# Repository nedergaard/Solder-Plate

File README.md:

🚀 This is a fork of [arwidcool/Solder-Plate](https://github.com/arwidcool/Solder-Plate). Please contribute to the original repository instead of this one.

---

# Solder Plate Controller with Detachable Hotplate

This repository contains the source code and design files for a Solder Plate Controller and detachable hotplate. The processor used is the ATmega4809 and is based on the work of DerSpatz. https://github.com/DerSpatz/PCB-reflow-solder-heat-plate

## Features
- Precise temperature control for soldering SMD components. with support of **up to 6 thermistors**.
- Cheap and widely available MCU- Atmega4809 and low BOM cost
- Custom PCB design with 2 versions: single area control (Completed) and 4 independent heating zones control(In works)
- Detacabale hotplate allows for use of new heatplate designs including larger ones
- Programming via USB
- PlatformIO integration for streamlined development.
- wifi via esp8266-12f module (with wifi version - In Development).
- Based on Reflow Hotplate by DerSpatz with some improvements
- Oled for menu navigation, debugging, and thermistor info
- TFT for reflow profile target and actual temp
- 4 buttons for menu navigation
- Current sense IC for current monitoring
- 3 indicator LED's. They work for both menu and REFLOW profiles (blinking while on the current stage and solid once the profile stage is complete).
- Buzzer for complete notification
- Buck- Converter for input voltage, allowing up to 24V in
- 24V+ rated input voltage stage components allowing  up to 24V to be used (Depending on powersupply trip option the "max" pwm needs to be lowered to not trip power suppply safety)
- Optional fan for cooling stage (not yet installed)
= Included are files for a case and a guard for the detachable plate terminal guard.

## Getting Started

### Prerequisites

- PlatformIO Core or PlatformIO IDE.
- ATmega4809 microcontroller and all the BOM components
- Basic soldering tools and electronic assembly skills.
- Access to a PCB manufacturing service or soldering equipment (solder paste, hot air gun, tweezers)
- Some basic technical skills

### Hardware Setup

*** MAKE SURE YOU ORDER THE HOTPLATE IN BLACK. IT WILL NOT DISCOLOR AND HOLDS UP A LOT BETTER TO HEAT CYCLES ***

1. **PCB Fabrication:** Fabricate the PCB using the provided gerber files. You can use these to order the naked PCB from services like JLCPCB. 
2. **Component Assembly:** Solder the components onto the PCB as per the schematic or choose a SMT assembly service like the ones from JLCPCB
3. **Power Supply Connection:** Choose a suitable power supply. 12V 5A tested, 24v 5A compatible. Use of more then 5A requires a appropriate FUSE to be chosen and solder on place of F1

### Preparing the ATmega4809

Before programming the ATmega4809, it needs to be flashed with a default bootloader.

1. **Bootloader Flashing:**

Same process as DerSpatz Solder plate with some changes to the bootloader settingffs:

The MCU can be programmed with JTAG2UPDI (https://github.com/ElTangas/jtag2updi). For programming, you need an Arduino with ATMEGA328p (Uno or Nano), some wires, a 4.7k resistor and a 10µF capacitor or 120 Ohm resistor to disable the auto-reset.

JCM from the Discord explained the process pretty good:

- Download/Clone this project: https://github.com/ElTangas/jtag2updi and rename the folder "source" to "jtag2updi" (otherwise the Arduino IDE won't like it)
- Open jtag2updi/jtag2updi.ino in your Arduino IDE
- Configure the flasher options for your Arduino Nano and flash it
- Connect D6 of your Arduino Nano over the 4.7kOhm resistor to the UPDI pin of the board and 5V to 5V and GND to 0V
- Add the MegaCoreX hardware package to the Ardunio IDE (see https://github.com/MCUdude/MegaCoreX#how-to-install)
- Select the options for the programmer **(Board: ATmega4809, Clock: Internal 16 MHz, BOD: 2.6V or 2.7V, EEPROM: retained, Pinout: 48 pin standard, Reset pin: Reset, Bootloader:Optiboot:Uart0(Defualt pins))** and select the port of your Ardunio Nano as Port
- Make sure the programmer selected is SerialUPDI or JTAG2UPDI
- Select Burn Bootloader and see if it runs through

2. **MicroUSB Programming And Firmware Upload:**

   - **Using Platformio:**
   1. After flashing the bootloader, the ATmega4809 can be programmed via the microUSB connection using PlatformIO by building the project and upload
  
   - **Using AVRDude:**
   1. Folow instructions on : https://github.com/ElTangas/jtag2updi?tab=readme-ov-file#using-with-avrdude
   2. Example : avrdude -c jtag2updi -P com7 -p t1614
  
   - **Using AVRDUDESS (AVRDUDE with GUI interface) -- This section many not be completley finished:**
   1. Download and install AVRDUDE https://download-mirror.savannah.gnu.org/releases/avrdude/
   2. Download AVRDUDESS : https://github.com/ZakKemble/AVRDUDESS
   3. Choose the programmer as arduino
   4. Choose the MCU as ATmega4809
   5. Choose the COMPORT where the Solder Plate Controller is connected to
   6. Choose the Flash binary in the programming directory -> set to Write
   7. Choose "Write" on the Flash option and press "Go"

3. **Setting up the controller**
   1. Order 100K NTC Glass thermistors  Use for dev was : 100K Ohm Resistor NTC 3950->  https://www.aliexpress.com/item/32862228715.html?spm=a2g0o.order_list.order_list_main.11.1f0a1802Lw8YGL
   2. Using either the potentiometer or soldering the resistor beside it choose the resistor reference value (2.5Kohm is standard)
   3. You can modify the thermistor settings in Global.ccp file, it is all explained in there
   4. Attach the sensors to the hotplate using High temp Kapton Tape
   5. Reccomended is 3 sensors on the bottom middle of plate all with 3 different refernece resistor values for accuracy across all temperature ranges and 1 thermistor held by a pair of helping hangs placed so the head touches somewhere on the PCB to be refllowed
   By default this is set as thermistor 1:
   6. Link to 2.0 inch TFT -> https://www.aliexpress.com/item/1005002363748586.html?spm=a2g0o.order_list.order_list_main.5.165d1802Amz1I7  (8 pin version) -> 7 Pin version can also be used 
   7. Link to 0.96 OLED -> https://www.aliexpress.com/item/32957309383.html?spm=a2g0o.order_list.order_list_main.17.662c1802iqqiSE  (Choose OLD design SSD1306)

   *** IMPORTANT: Thermistors 1 is ONLY available on the hotplate. Thermistor 6 is only available on the controller via connector 5**

   You can solder the thermistors directly on the hotplatte or use them with the connector. Please update the thermistor settings to the way you have them set-up.

   Here are the defualt thermistor settings, The assume that the thermistors are soldered on the plate for 1,2,3: 
   Thermistors 6 on the connector number 5, touching the PCB to be soldered.

   Thermistor thermistor1(THERMISTOR1_PIN, 2545, ThermistorZ_Placement::ON_PCB, ThermistorXY_Placement::MIDDLE);          // -> 2545ohm set refrence -> This thermistor is set directly touching the PCB to be soldered
   Thermistor thermistor2(THERMISTOR2_PIN, 9100, ThermistorZ_Placement::BOTTOM, ThermistorXY_Placement::MIDDLE_LOW_TEMP);          //- > 9100 ohm set refrence Best accuracy around 90C -> This thermistor is used for the lower end of the temp scale  
   Thermistor thermistor3(THERMISTOR3_PIN, 2040, ThermistorZ_Placement::BOTTOM, ThermistorXY_Placement::MIDDLE); // -> 2.5Kohm best middleground
   Thermistor thermistor4(THERMISTOR4_PIN, 564, ThermistorZ_Placement::BOTTOM, ThermistorXY_Placement::MIDDLE_HIGH_TEMP); //-> 564Kohm set refrence // 564R reference = Best accuracy around 210C

   If you wish to only use the connectors use 2,3,4 and update the Globals .cpp to match your settings
      
   The set resistence is measured between a GND point anywhere on the board and the LEFT pin of the connector with the thermistor UNPLUGGED and the MODULE POWERED OFF!!!!

   you can measure and set those to the preset values or modify the values in globals.ccp to match your thermistors.

   If a thermistor is set to bottom a automatic scaling factor for the difference difference in plate temp is set that was aquired through lots of datalogging and computations

   If a thermistor is set to SIDE there is no scaling factor and will throw off the reading acorss the center of the plate (overall will be lower)

   When using the Thermistor with placement "ON_PCB" That thermistor has a weighting factor of 10 and has the biggest effect on the read temperature.

   The normal weighting factor is between 0.1 and 1.5 for the others.

### Software Installation

1. **Clone the Repository:**
   ```bash
   git clone https://github.com/arwidcool/Solder-Plate
   cd Solder-Plate
2. **Import in vscode**
To open a PlatformIO project in VSCode with the PlatformIO extension, follow these steps:

1. Launch VSCode and ensure that you have the PlatformIO extension installed. If not, you can install it from the VSCode marketplace.
2. Open the VSCode command palette by pressing Ctrl+Shift+P (Windows/Linux) or Cmd+Shift+P (Mac).
3. In the command palette, type "PlatformIO: Open" and select the "PlatformIO: Open" command from the list.
4. Navigate to the root folder of your PlatformIO project using the file explorer that appears.
5. Select the folder and click "Open" to open the PlatformIO project in VSCode.

### Usage

Power On: Connect the controller with a 12V 5A(Tested working) or 24V 5A PSU (Untested)
Set Profile: Navigate the menu and choose the desired reflow profile
Start Soldering: Place your PCB and components on the hotplate and start the profile

### Customization

Feel free to modify the firmware and PCB design to suit your specific needs.

### Contributing
Contributions are welcome. Please follow standard procedures for contributing to open-source projects.

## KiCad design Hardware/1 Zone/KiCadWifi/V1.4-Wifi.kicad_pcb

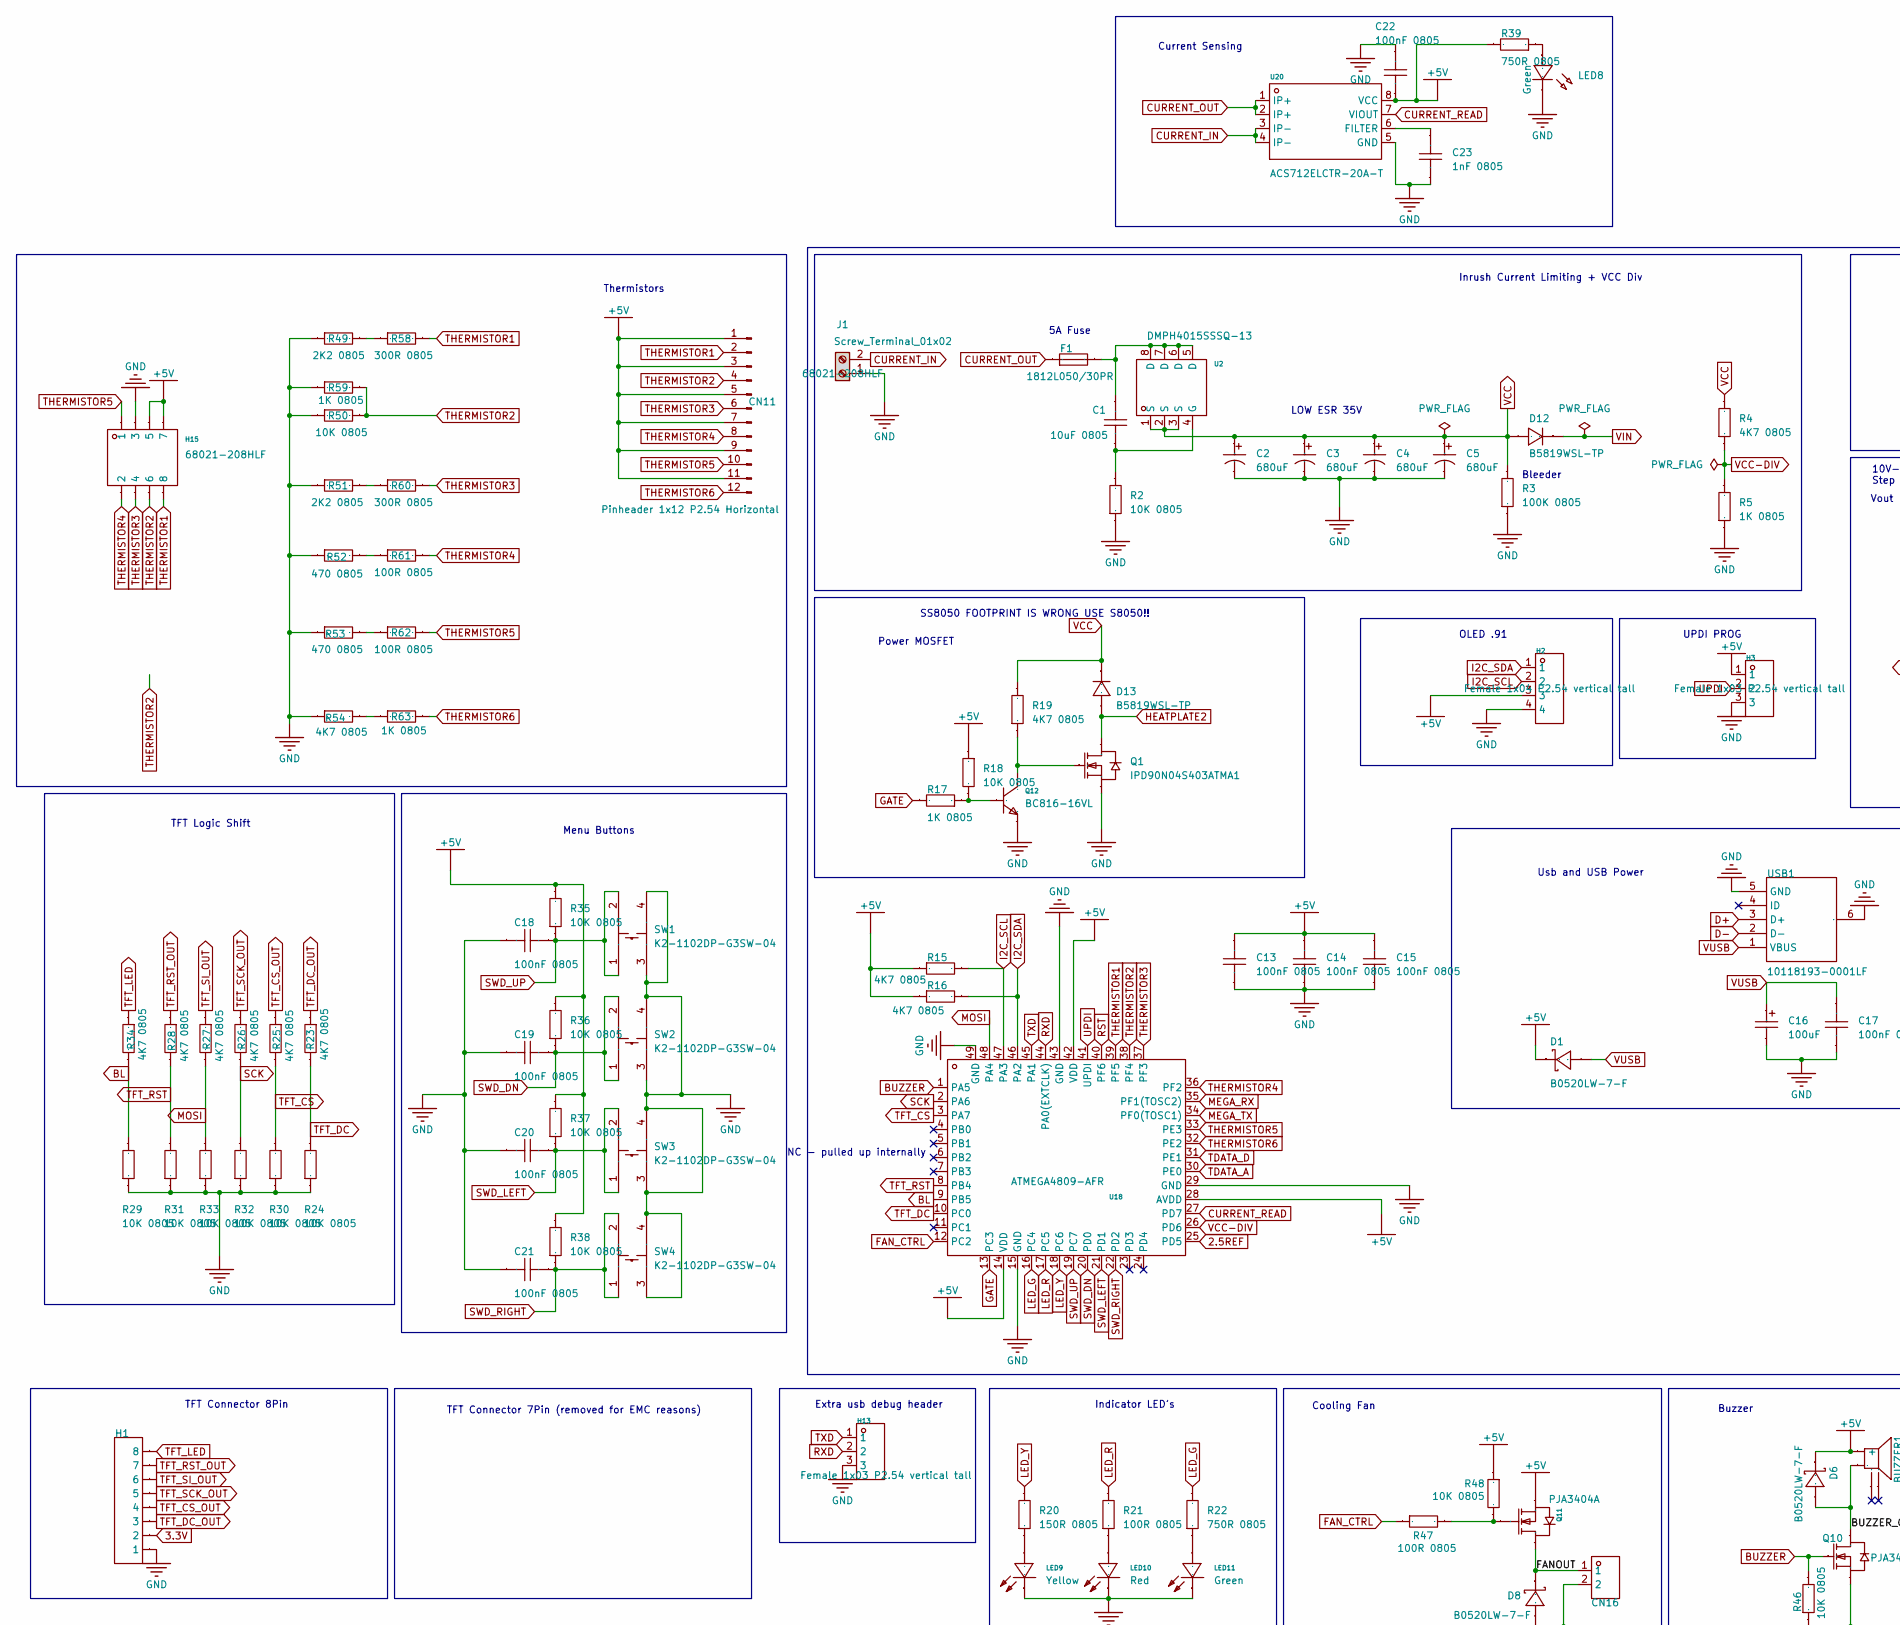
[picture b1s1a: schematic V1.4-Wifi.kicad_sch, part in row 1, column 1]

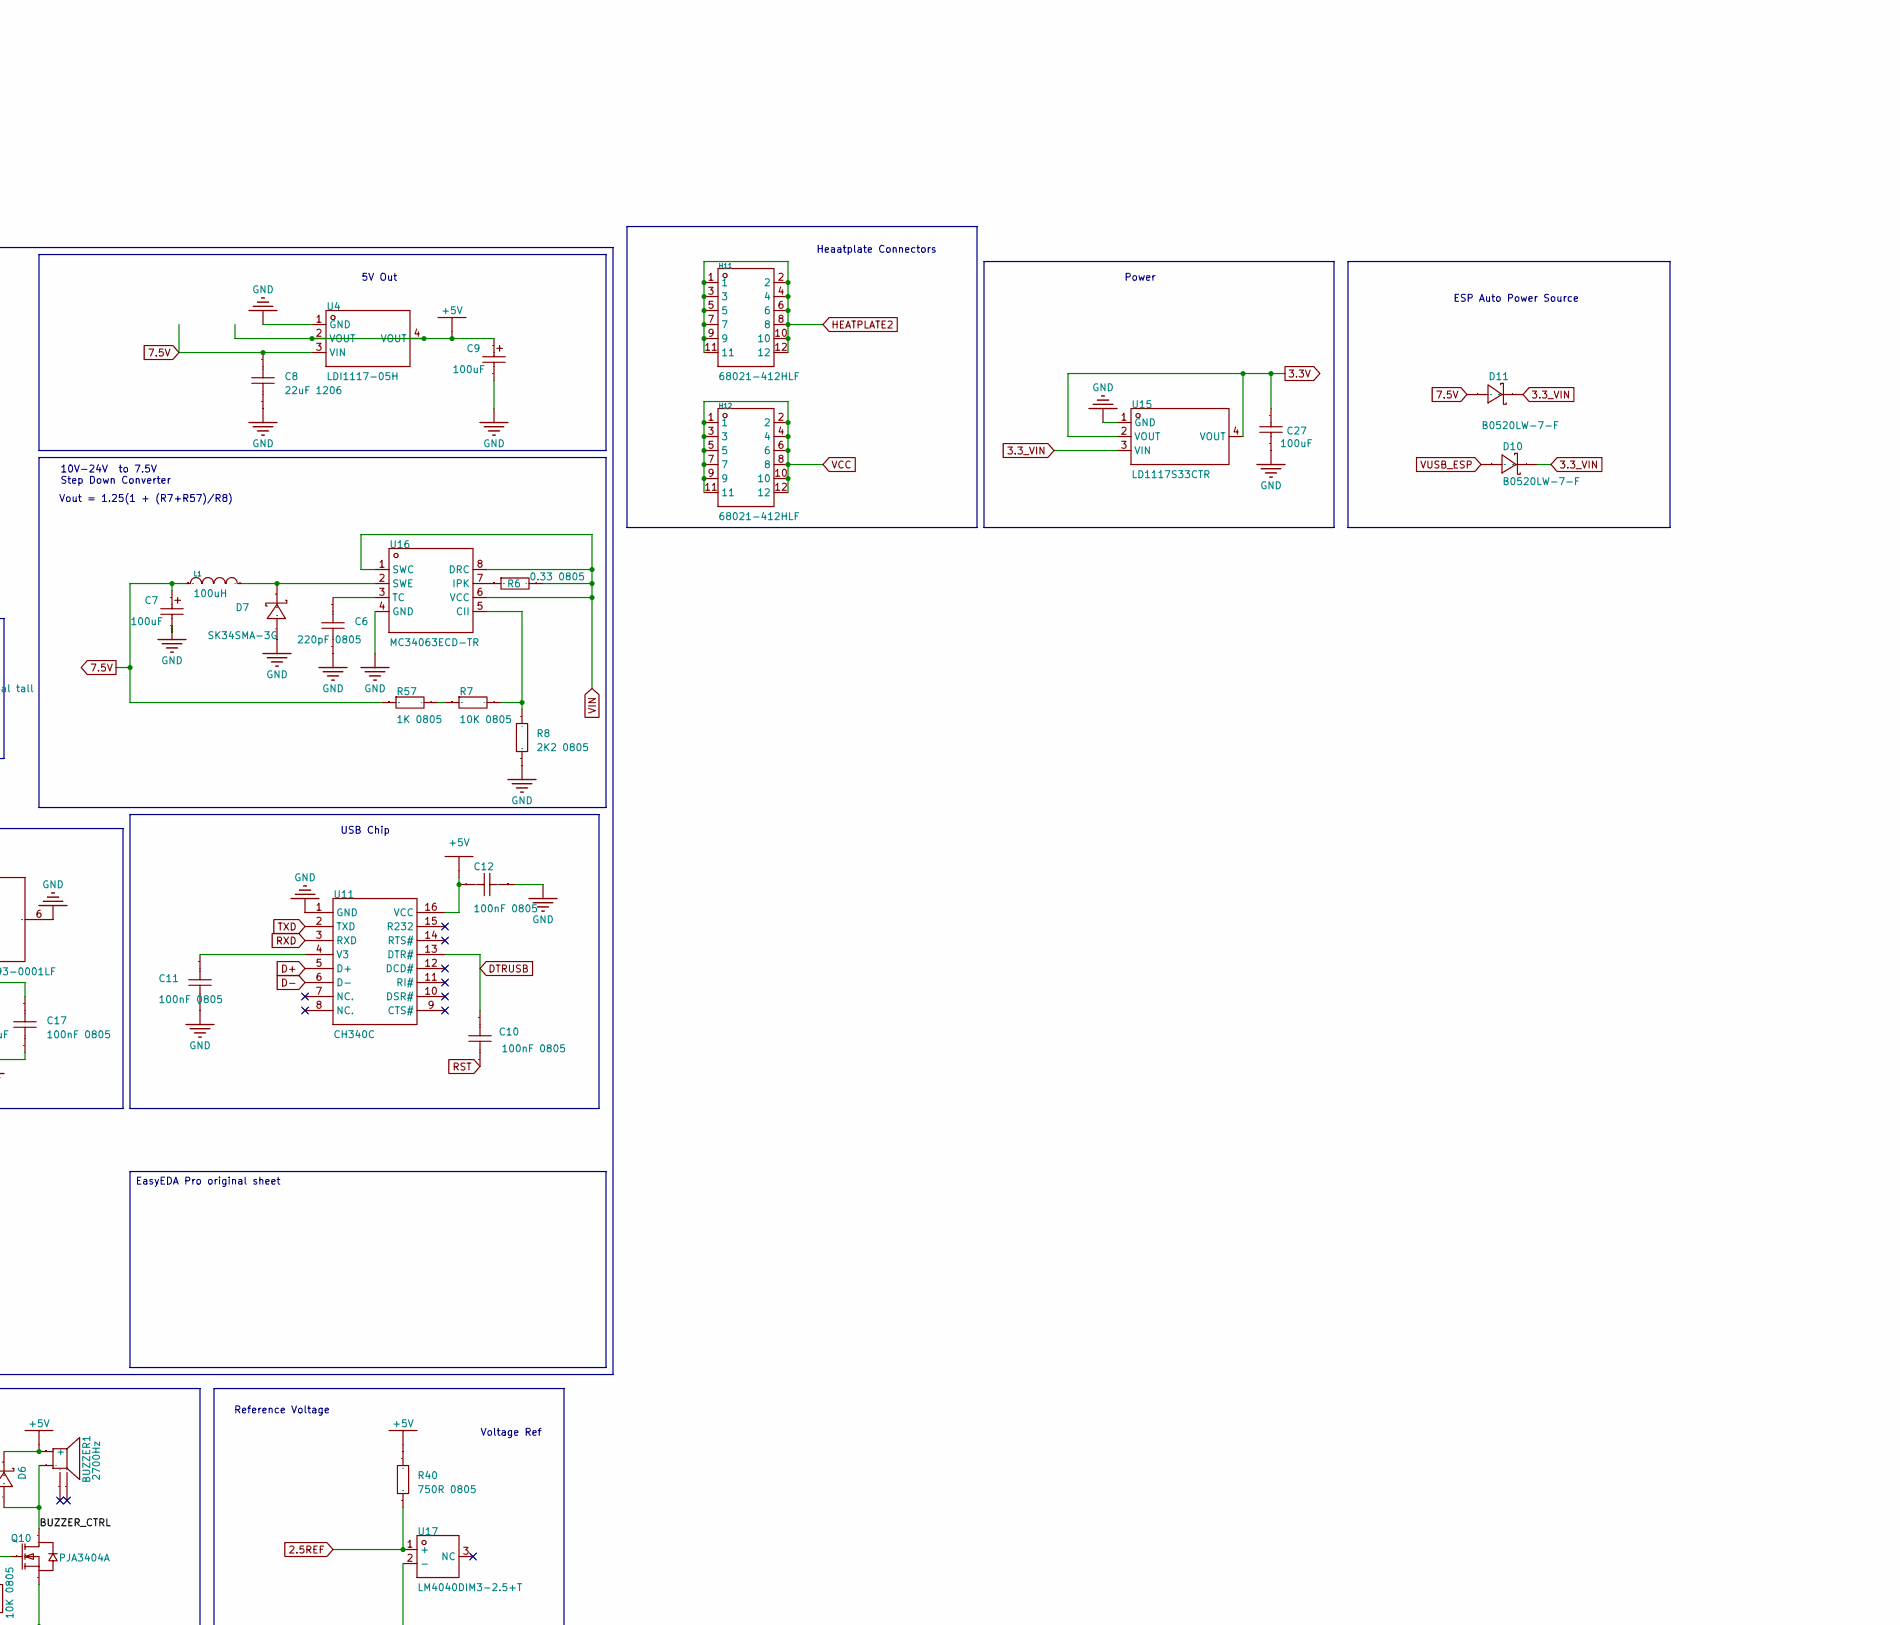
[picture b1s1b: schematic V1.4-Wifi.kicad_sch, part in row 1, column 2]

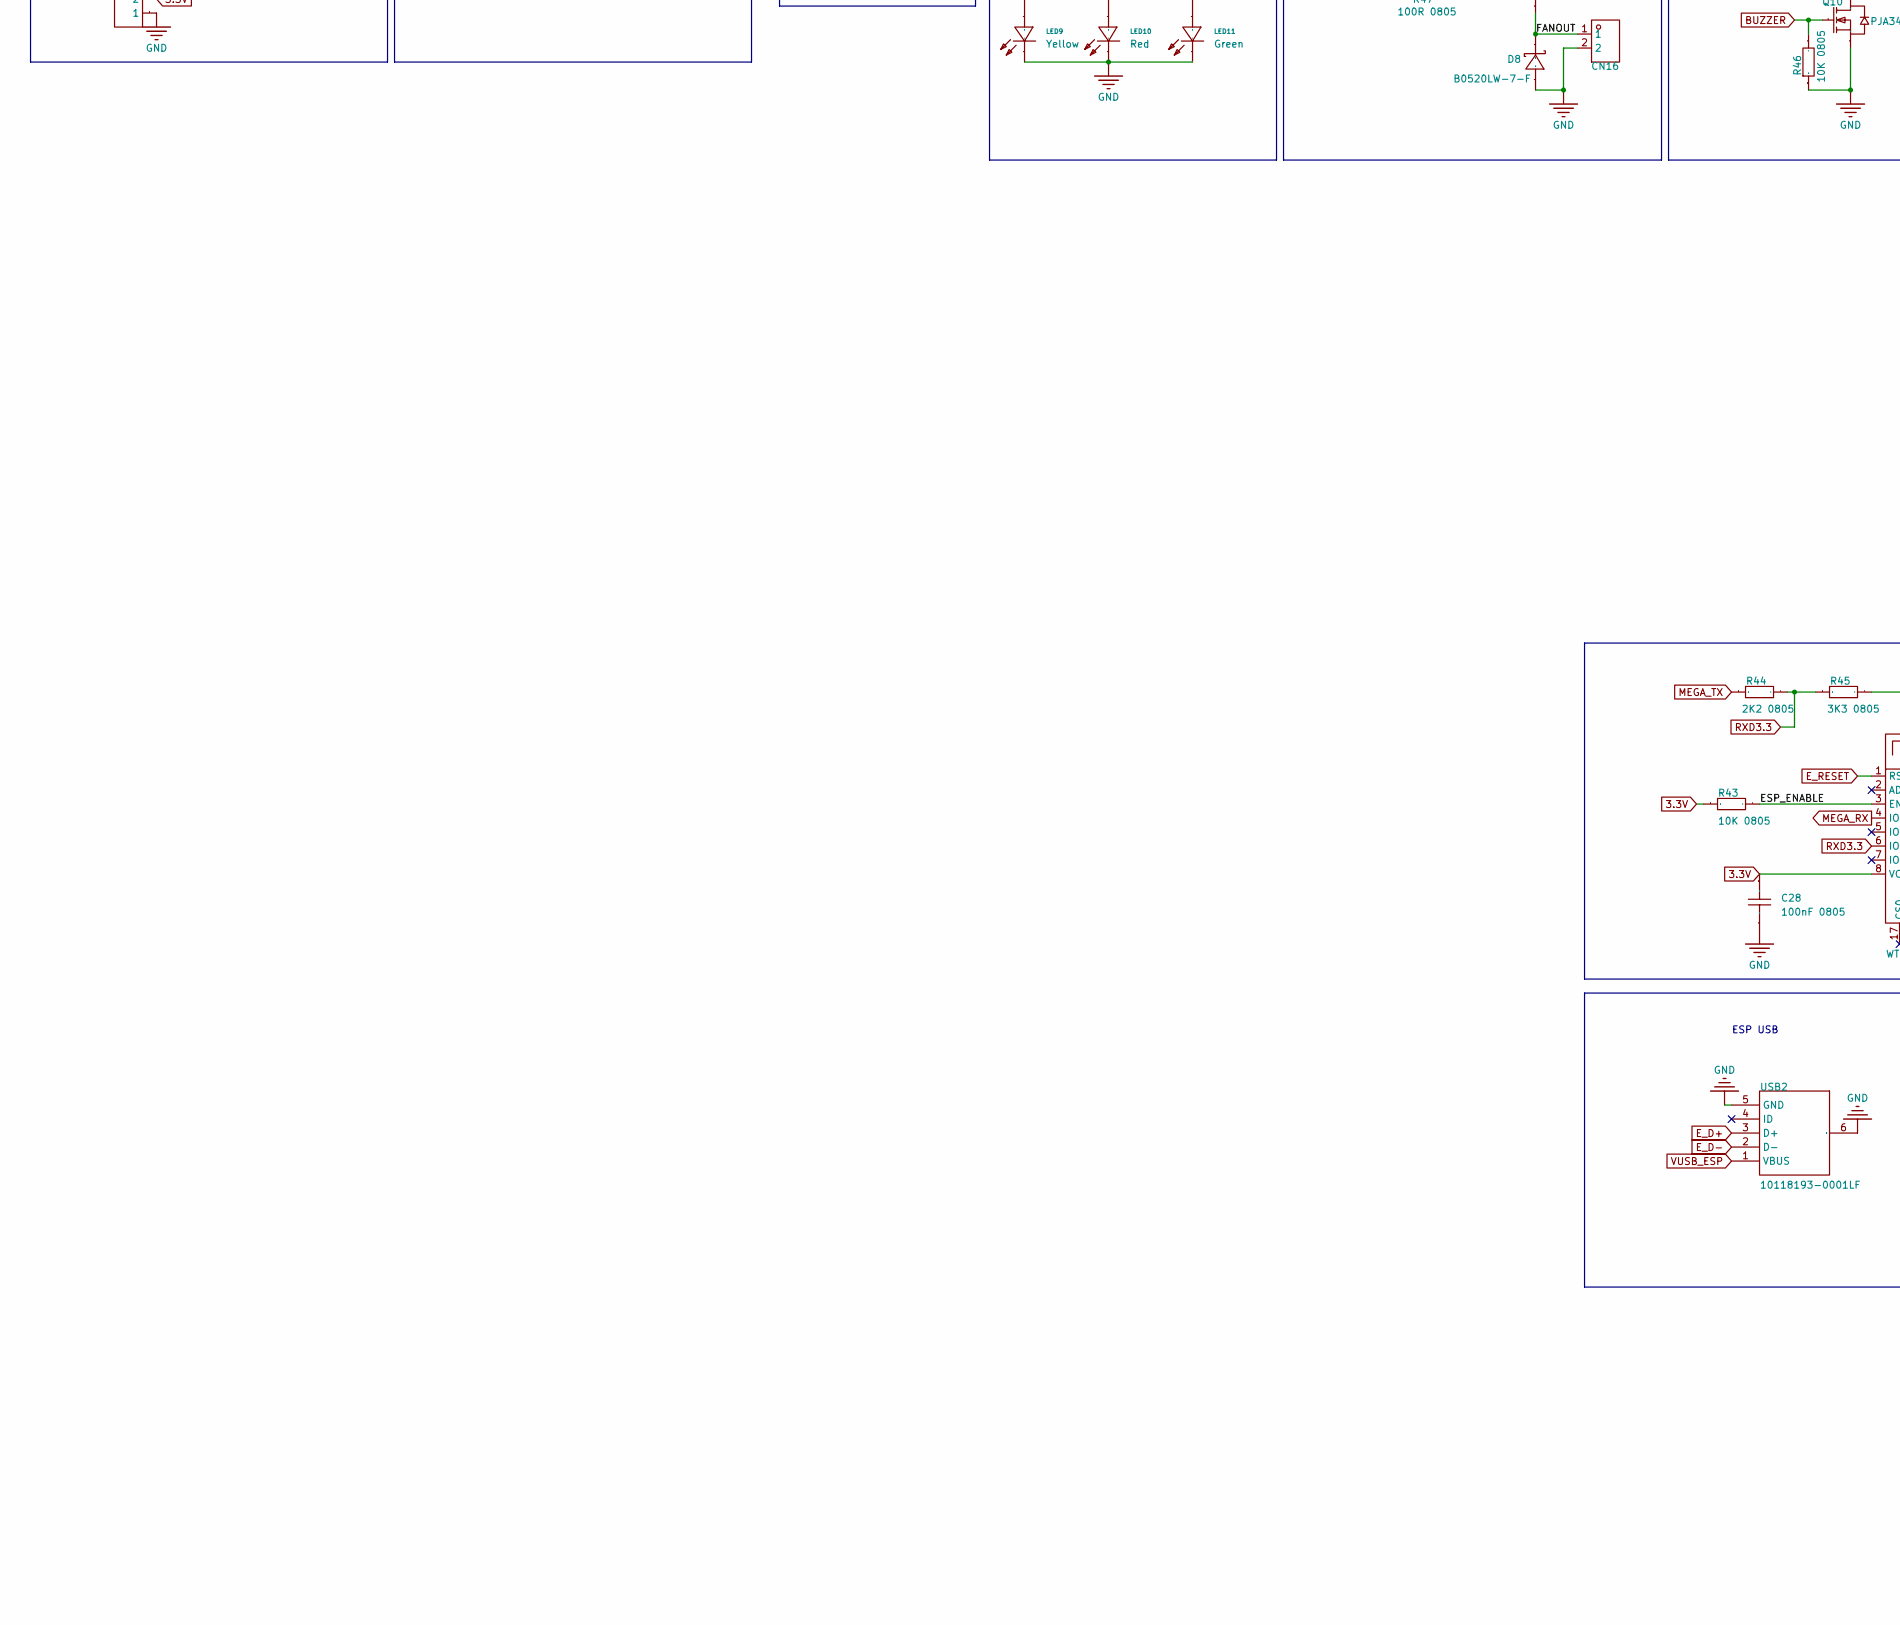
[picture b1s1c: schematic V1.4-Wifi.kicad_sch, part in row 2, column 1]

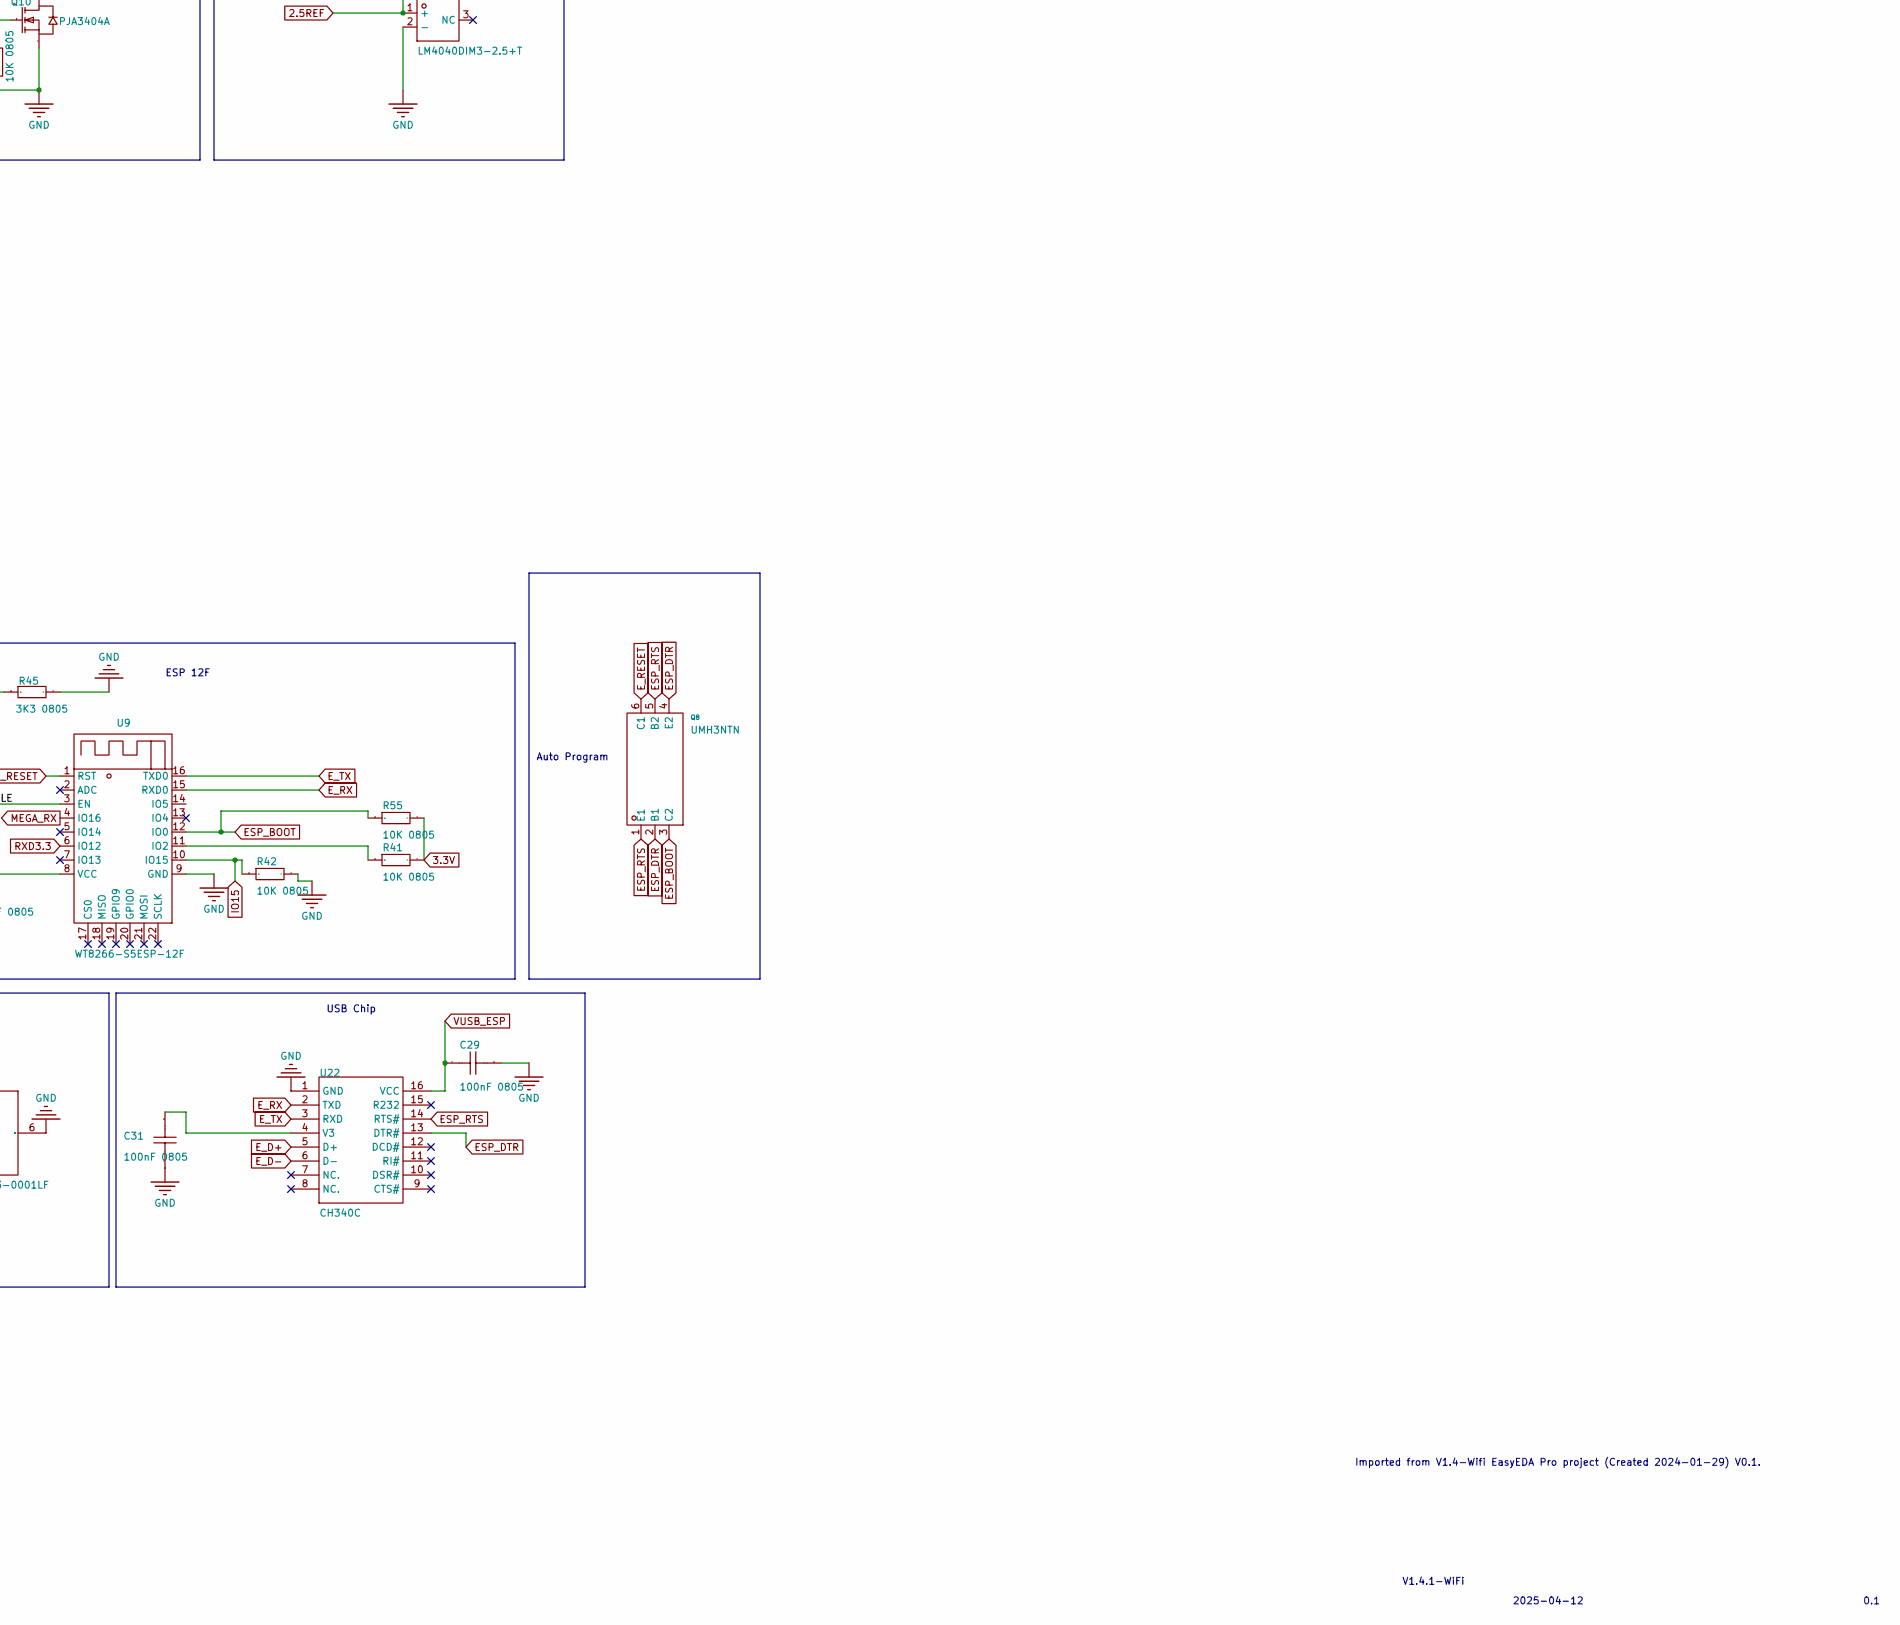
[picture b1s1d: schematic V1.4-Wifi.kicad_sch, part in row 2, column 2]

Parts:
BUZZER1: 2700Hz; MagneticBuzzer_CUI_CMT-8504-100-SMT; mpn CMT-8530S-SMT-TRCMT-8504-100-SMT-TR
C1: 10uF 0805; C0805
C2, C3, C4, C5: 680uF; CP_Radial_D10.0mm_P5.00mm; mpn EEU-FR1V681B; LCSC Part Name 680uF±20%35V
C6: 220pF 0805; C0805
C7, C9, C16: 100uF; CAP-SMD_L3.5-W2.8-R-RD; mpn T491B107M010AT; LCSC Part Name 100uF ±20% 16V
C8: 22uF 1206; C_1206_3216Metric_Pad1.33x1.80mm_HandSolder
C10, C11, C12, C13, C14, C15, C17, C18, C19, C20, C21, C22, C28, C29, C31: 100nF 0805; C0805
C23: 1nF 0805; C0805
C27: 100uF; CAP-SMD_L3.5-W2.8-R-RD; mpn T491B107M010AT; LCSC Part Name 100uF±20%6.3V
CN11: Pinheader 1x12 P2.54 Horizontal; PinHeader_1x12_P2.54mm_Horizontal
CN16: Pinheader 1x02 P2.54 Horizontal; PinHeader_1x02_P2.54mm_Horizontal
D1, D6, D8, D10, D11: B0520LW-7-F; SOD-123_L2.8-W1.8-LS3.7-RD; mpn B0520LW-7-F; LCSC Part Name 20V500mA450mV@500mA
D7: SK34SMA-3G; D_SMA_Handsoldering; mpn SK34SMA-3G
D12, D13: B5819WSL-TP; D_SOD-323F; mpn B5819WSL-TP; LCSC Part Name B5819W
F1: 1812L050/30PR; Fuse_1812_4532Metric; mpn 1812L050/30PR; LCSC Part Name 5A
H1: Female 1x08 P2.54 vertical tall; HDR-TH_8P-P2.54-V-F-1
H2: Female 1x04 P2.54 vertical tall; HDR-TH_4P-P2.54-V-F; mpn 2.54-1*4P母; JLCPCB Part Class Extended Part
H3, H13: Female 1x03 P2.54 vertical tall; HDR-TH_3P-P2.54-V-F; mpn PM254V-11-03-H85; JLCPCB Part Class Extended Part
H11, H12: 68021-412HLF; HDR-TH_12P-P2.54-H-F-R2-C6-S2.54-W10.2; mpn 68021-412HLF; LCSC Part Name 2.54mm2x6P
H15: 68021-208HLF; HDR-TH_8P-P2.54-H-F-R2-C4-S2.54-W10.2; mpn A2541HWR-2x4P; LCSC Part Name 间距:2.54mm2x4P弯插
J1: Screw_Terminal_01x02; TerminalBlock_Phoenix_MKDS-1,5-2_1x02_P5.00mm_Horizontal; mpn 68021-208HLF
L1: 100uH; L_Coilcraft_MSS1048-XXX; mpn MSS1048-104MLC
LED8: Green; LED0805-RD_GREEN; mpn LTST-C171KGKT
LED9: Yellow; LED1206-RD; mpn LTST-C150YKT; LCSC Part Name 橙灯1206橙色正贴
LED10: Red; LED1206-RD; mpn LTST-C250KRKT; LCSC Part Name 橙灯1206橙色正贴
LED11: Green; LED1206-RD; mpn LTST-C150KGKT; LCSC Part Name 橙灯1206橙色正贴
Q1: IPD90N04S403ATMA1; TO-252-2_L6.6-W6.1-P4.57-LS9.9-TL-CW; mpn IPD90N04S403ATMA1; LCSC Part Name N沟道40V13A50A
Q8: UMH3NTN; SOT-363_L2.0-W1.3-P0.65-LS2.1-TL; mpn UMH3NTN; LCSC Part Name 电流:100mA耐压:50V
Q10: PJA3404A; SOT-23-3; mpn PJA3404A_R1_00001; LCSC Part Name N沟道20V4.2A
Q11: PJA3404A; SOT-23-3; mpn PJA3404A_R1_00001; LCSC Part Name N沟道耐压:20V电流:6A
Q12: BC816-16VL; SOT-23-3; mpn BC816-16VL; LCSC Part Name 电流:500mA 耐压:25V
R2, R7, R18, R24, R29, R30, R31, R32, R33, R35, R36, R37, R38, R41, R42, R43, R46, R48, R50, R55: 10K 0805; R_0805_2012Metric_Pad1.20x1.40mm_HandSolder
R3: 100K 0805; R_0805_2012Metric_Pad1.20x1.40mm_HandSolder
R4, R15, R16, R19, R23, R25, R26, R27, R28, R34, R54: 4K7 0805; R_0805_2012Metric_Pad1.20x1.40mm_HandSolder
R5, R17, R57, R59, R63: 1K 0805; R_0805_2012Metric_Pad1.20x1.40mm_HandSolder
R6: 0.33 0805; R_0805_2012Metric_Pad1.20x1.40mm_HandSolder; mpn KRL1220E-M-R330-F
R8, R44, R49, R51: 2K2 0805; R_0805_2012Metric_Pad1.20x1.40mm_HandSolder
R20: 150R 0805; R_0805_2012Metric_Pad1.20x1.40mm_HandSolder
R21, R47, R61, R62: 100R 0805; R_0805_2012Metric_Pad1.20x1.40mm_HandSolder
R22, R39, R40: 750R 0805; R_0805_2012Metric_Pad1.20x1.40mm_HandSolder
R45: 3K3 0805; R_0805_2012Metric_Pad1.20x1.40mm_HandSolder
R52, R53: 470 0805; R_0805_2012Metric_Pad1.20x1.40mm_HandSolder
R58, R60: 300R 0805; R_0805_2012Metric_Pad1.20x1.40mm_HandSolder
SW1, SW2, SW3, SW4: K2-1102DP-G3SW-04; KEY-TH_4P-L6.0-W6.0-P4.50-LS6.5; mpn K2-1102DP-G3SW-04; LCSC Part Name 6*6*7
U2: DMPH4015SSSQ-13; SOIC-8_3.9x4.9mm_P1.27mm
U4: LDI1117-05H; SOT-223
U9: WT8266-S5ESP-12F; WIFIM-SMD_22P-L24.0-W16.0-P2.00; mpn WT8266-S5ESP-12F
U11, U22: CH340C; SOP-16_L10.0-W3.9-P1.27-LS6.0-BL; mpn CH340C; LCSC Part Name CH340C
U15: LD1117S33CTR; SOT-223
U16: MC34063ECD-TR; SOIC-8_3.9x4.9mm_P1.27mm; mpn MC34063ECD-TR; LCSC Part Name 升降压型Vin=3V~40VVout=1.25V~38V1.5A
U17: LM4040DIM3-2.5+T; SOT-23-3; mpn LM4040DIM3-2.5+T; LCSC Part Name LM4040DIM3-2.5+T
U18: ATMEGA4809-AFR; TQFP-48-1EP_7x7mm_P0.5mm_EP3.5x3.5mm; mpn ATMEGA4809-AFR
U20: ACS712ELCTR-20A-T; SOIC-8_L4.9-W3.9-P1.27-LS6.0-BL; mpn ACS712ELCTR-20A-T; LCSC Part Name ACS712ELCTR-20A-T
USB1: 10118193-0001LF; USB_Micro-B_Amphenol_10118193-0001LF_Horizontal; mpn 10118193-0001LF
USB2: 10118193-0001LF; USB_Micro-B_Amphenol_10118193-0001LF_Horizontal; mpn 10118193-0001LF; LCSC Part Name Micro-B母座卧贴

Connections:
2.5REF: R40.1, U17.1 (+), U18.25 (PD5)
3.3V: C27.2, C28.1, H1.2, R41.2, R43.1, R55.2, U9.8 (VCC), U15.2 (VOUT), U15.4 (VOUT)
3.3_VIN: D10.1 (K), D11.1 (K), U15.3 (VIN)
7.5V: C7.1, C8.2, D11.2 (A), L1.1, R57.1, U4.3 (VIN)
+5V: BUZZER1.1 (+), C9.1, C12.2, C13.1, C14.1, C15.1, C22.2, CN11.1, CN11.3, CN11.5, CN11.7, CN11.9, CN11.11, D1.1 (K), D6.1 (K), H2.3, H3.1, H15.5, H15.7, Q11.2 (S), R15.1, R16.1, R18.1, R35.2, R36.2, R37.2, R38.2, R39.2, R40.2, R48.1, U4.2 (VOUT), U4.4 (VOUT), U11.16 (VCC), U18.14 (VDD), U18.28 (AVDD), U18.42 (VDD), U20.8 (VCC)
/BUZZER_CTRL: BUZZER1.2, D6.2 (A), Q10.3 (D)
/ESP_ENABLE: R43.2, U9.3 (EN)
/FANOUT: CN16.1, D8.1 (K), Q11.3 (D)
BL: R29.2, R34.2, U18.9 (PB5)
BUZZER: Q10.1 (G), R46.2, U18.1 (PA5)
CURRENT_IN: J1.2, U20.3 (IP-), U20.4 (IP-)
CURRENT_OUT: F1.1, U20.1 (IP+), U20.2 (IP+)
CURRENT_READ: U18.27 (PD7), U20.7 (VIOUT)
D+: U11.5 (D+), USB1.3 (D+)
D-: U11.6 (D-), USB1.2 (D-)
DTRUSB: C10.1, U11.13 (DTR#)
ESP_BOOT: Q8.3 (C2), R55.1, U9.12 (IO0)
ESP_DTR: Q8.2 (B1), Q8.4 (E2), U22.13 (DTR#)
ESP_RTS: Q8.1 (E1), Q8.5 (B2), U22.14 (RTS#)
E_D+: U22.5 (D+), USB2.3 (D+)
E_D-: U22.6 (D-), USB2.2 (D-)
E_RESET: Q8.6 (C1), U9.1 (RST)
E_RX: U9.15 (RXD0), U22.2 (TXD)
E_TX: U9.16 (TXD0), U22.3 (RXD)
FAN_CTRL: R47.1, U18.12 (PC2)
GATE: R17.2, U18.13 (PC3)
GND: C2.2, C3.2, C4.2, C5.2, C6.2, C7.2, C8.1, C9.2, C11.2, C12.1, C13.2, C14.2, C15.2, C16.2, C17.2, C18.2, C19.2, C20.2, C21.2, C22.1, C23.2, C27.1, C28.2, C29.1, C31.2, CN16.2, D7.2 (A), D8.2 (A), H1.1, H2.4, H3.3, H13.3, H15.3, J1.1, LED8.2 (C), LED9.1 (-), LED10.1 (-), LED11.1 (-), Q1.3 (S), Q10.2 (S), Q12.2 (E), R2.1, R3.1, R5.1, R8.1, R24.1, R29.1, R30.1, R31.1, R32.1, R33.1, R42.2, R45.2, R46.1, R49.1, R50.1, R51.1, R52.1, R53.1, R54.1, R59.1, SW1.3, SW1.4, SW2.3, SW2.4, SW3.3, SW3.4, SW4.3, SW4.4, U4.1 (GND), U9.9 (GND), U11.1 (GND), U15.1 (GND), U16.4 (GND), U17.2 (-), U18.15 (GND), U18.29 (GND), U18.43 (GND), U18.49 (GND), U20.5 (GND), U22.1 (GND), USB1.5 (GND), USB1.6 (EH), USB2.5 (GND), USB2.6 (EH)
HEATPLATE2: D13.2, H11.1, H11.2, H11.3, H11.4, H11.5, H11.6, H11.7, H11.8, H11.9, H11.10, H11.11, H11.12, Q1.2 (D)
I2C_SCL: H2.2, R15.2, U18.47 (PA3)
I2C_SDA: H2.1, R16.2, U18.46 (PA2)
IO15: R42.1, U9.10 (IO15)
LED_G: R22.2, U18.16 (PC4)
LED_R: R21.2, U18.17 (PC5)
LED_Y: R20.2, U18.18 (PC6)
MEGA_RX: U9.4 (IO16), U18.35 (PF1(TOSC2))
MEGA_TX: R44.1, U18.34 (PF0(TOSC1))
MOSI: R27.2, R33.2, U18.48 (PA4)
unnamed: C1.1, F1.2, U2.5 (D), U2.6 (D), U2.7 (D), U2.8 (D)
unnamed: D7.1 (K), L1.2, U16.2 (SWE)
unnamed: LED8.1 (A), R39.1
unnamed: LED9.2 (+), R20.1
unnamed: LED10.2 (+), R21.1
unnamed: LED11.2 (+), R22.1
unnamed: Q1.1 (G), Q12.3 (C), R19.1
unnamed: Q11.1 (G), R47.2, R48.2
unnamed: Q12.1 (B), R17.1, R18.2
unnamed: R49.2, R58.1
unnamed: R51.2, R60.1
unnamed: R52.2, R61.1
unnamed: R53.2, R62.1
unnamed: R54.2, R63.1
unnamed: R7.1, R57.2
unnamed: C1.2, R2.2, U2.4 (G)
unnamed: R41.1, U9.11 (IO2)
unnamed: C11.1, U11.4 (V3)
unnamed: R7.2, R8.2, U16.5 (CII)
unnamed: R6.1, U16.7 (IPK)
unnamed: C6.1, U16.3 (TC)
unnamed: C23.1, U20.6 (FILTER)
unnamed: C31.1, U22.4 (V3)
RST: C10.2, U18.40 (PF6)
RXD: H13.2, U11.3 (RXD), U18.44 (PA0(EXTCLK))
RXD3.3: R44.2, R45.1, U9.6 (IO12)
SCK: R26.2, R32.2, U18.2 (PA6)
SWD_DN: C19.1, R36.1, SW2.1, SW2.2, U18.20 (PD0)
SWD_LEFT: C20.1, R37.1, SW3.1, SW3.2, U18.21 (PD1)
SWD_RIGHT: C21.1, R38.1, SW4.1, SW4.2, U18.22 (PD2)
SWD_UP: C18.1, R35.1, SW1.1, SW1.2, U18.19 (PC7)
TDATA_A: U18.30 (PE0)
TDATA_D: U18.31 (PE1)
TFT_CS: R25.2, R30.2, U18.3 (PA7)
TFT_CS_OUT: H1.4, R25.1
TFT_DC: R23.2, R24.2, U18.10 (PC0)
TFT_DC_OUT: H1.3, R23.1
TFT_LED: H1.8, R34.1
TFT_RST: R28.2, R31.2, U18.8 (PB4)
TFT_RST_OUT: H1.7, R28.1
TFT_SCK_OUT: H1.5, R26.1
TFT_SI_OUT: H1.6, R27.1
THERMISTOR1: CN11.2, H15.8, R58.2, U18.39 (PF5)
THERMISTOR2: CN11.4, H15.6, R50.2, R59.2, U18.38 (PF4)
THERMISTOR3: CN11.6, H15.4, R60.2, U18.37 (PF3)
THERMISTOR4: CN11.8, H15.2, R61.2, U18.36 (PF2)
THERMISTOR5: CN11.10, H15.1, R62.2, U18.33 (PE3)
THERMISTOR6: CN11.12, R63.2, U18.32 (PE2)
TXD: H13.1, U11.2 (TXD), U18.45 (PA1)
UPDI: H3.2, U18.41 (UPDI)
VCC: C2.1, C3.1, C4.1, C5.1, D12.2, D13.1, H12.1, H12.2, H12.3, H12.4, H12.5, H12.6, H12.7, H12.8, H12.9, H12.10, H12.11, H12.12, R3.2, R4.2, R19.2, U2.1 (S), U2.2 (S), U2.3 (S)
VCC-DIV: R4.1, R5.2, U18.26 (PD6)
VIN: D12.1, R6.2, U16.1 (SWC), U16.6 (VCC), U16.8 (DRC)
VUSB: C16.1, C17.1, D1.2 (A), USB1.1 (VBUS)
VUSB_ESP: C29.2, D10.2 (A), U22.16 (VCC), USB2.1 (VBUS)

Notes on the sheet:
Thermistors
Extra usb debug header
Menu Buttons
UPDI PROG
SS8050 FOOTPRINT IS WRONG USE S8050!!
USB Chip
NC - pulled up internally
Auto Program
Vout = 1.25(1 + (R7+R57)/R8)
10V-24V to 7.5V Step Down Converter
Buzzer
TFT Connector 7Pin (removed for EMC reasons)
Bleeder
ESP Auto Power Source
Power
ESP USB
Cooling Fan
Usb and USB Power
TFT Logic Shift
Voltage Ref
2025-04-12
OLED .91
Power MOSFET
LOW ESR 35V
Current Sensing
V1.4.1-WiFi
5A Fuse
0.1
TFT Connector 8Pin
Reference Voltage
Heaatplate Connectors
Inrush Current Limiting + VCC Div
5V Out
Indicator LED's
Imported from V1.4-Wifi EasyEDA Pro project (Created 2024-01-29) V0.1.
ESP 12F
EasyEDA Pro original sheet
